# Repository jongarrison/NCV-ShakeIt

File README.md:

# NCV-ShakeIt
## (Non Contact Voltage Detecting Time Delayed Relay With Audio Feedback)

<div style="width: 100%; text-align: center;">
    
</div>

This device is designed to turn on two relays (currently for a single two phase motor) after detecting that another AC device has shut off. The running of the other AC device is detected using a Non-contact Voltage (NCV) detector. When the device is about to trigger the relays, it plays some audio feedback (mp3 files) to let people know the motor is about to run.

Basic functions:
* Device has an antenna for detecting 60hz AC power in a nearby wire. If AC is detected for longer than a minimum threshold the system is ready to trigger when the AC next shuts off. The sensitivity of the AC detection is controlled by a potentiometer knob.
* The device waits for some interval while the main motor system spools down. During this spool down period audio is played to indicate what is happening.
* After the spool down period, two relays are turned on for an interval set by another potentiometer knob. 

# Technical Details

### Non-contact Voltage Detector circuit and algorithm
* Based on this very cool project: https://www.instructables.com/Contactless-AC-Detector/

### PCB Design
* Kicad files are provided in ./PCB_NCV-ShakeIt

<div style="width: 100%; text-align: center;">
    
</div>

### Enclosure Design
* Done in Rhino3D Grasshopper. Files found in ./ShakeIt_enclosure

<div style="width: 100%; text-align: center;">
    
</div>

### Microcontroller
* [Seeed Xiao SAMD21 board](https://wiki.seeedstudio.com/Seeeduino-XIAO/) - [Pinout](https://wiki.seeedstudio.com/Seeeduino-XIAO/#hardware-overview)

### MP3 Playback - DFPlayer
* [Usage Tips](https://reprage.com/posts/2018-05-08-dfplayer-mini-cheat-sheet/)

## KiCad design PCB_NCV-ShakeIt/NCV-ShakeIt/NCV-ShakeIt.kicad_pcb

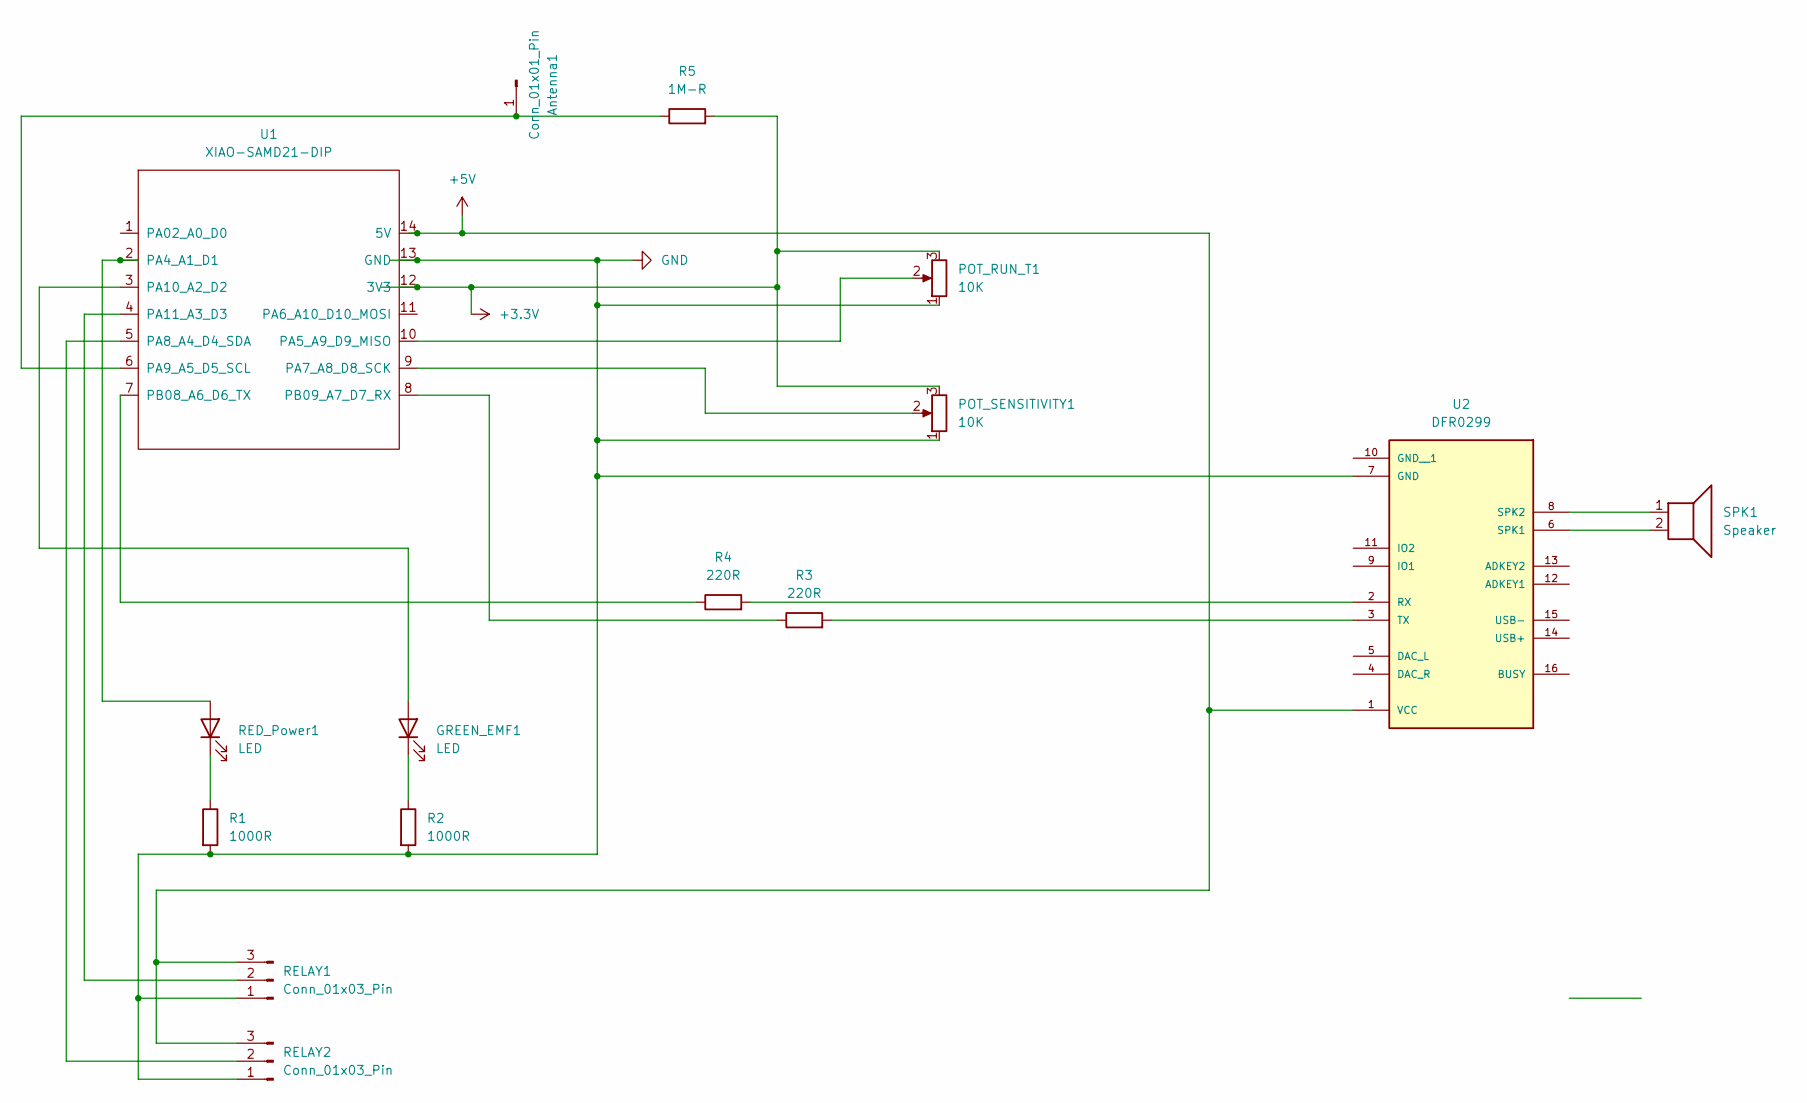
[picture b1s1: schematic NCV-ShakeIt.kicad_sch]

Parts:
Antenna1: Conn_01x01_Pin; PinHeader_1x01_P2.54mm_Vertical
GREEN_EMF1: LED; LED_D5.0mm
POT_RUN_T1: 10K; JG-3Pin-Pot-11mmOuterPins
POT_SENSITIVITY1: 10K; JG-3Pin-Pot-11mmOuterPins
R1, R2: 1000R; R_Axial_DIN0207_L6.3mm_D2.5mm_P10.16mm_Horizontal
R3, R4: 220R; R_Axial_DIN0207_L6.3mm_D2.5mm_P10.16mm_Horizontal
R5: 1M-R; R_Axial_DIN0207_L6.3mm_D2.5mm_P10.16mm_Horizontal
RED_Power1: LED; LED_D5.0mm
RELAY1, RELAY2: Conn_01x03_Pin; PinHeader_1x03_P2.54mm_Vertical
SPK1: Speaker; PinHeader_1x02_P2.54mm_Vertical
U1: XIAO-SAMD21-DIP
U2: DFR0299; MODULE_DFR0299

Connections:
+3.3V: POT_RUN_T1.3, POT_SENSITIVITY1.3, R5.2, U1.12 (3V3)
+5V: RELAY1.3, RELAY2.3, U1.14 (5V), U2.1 (VCC)
GND: POT_RUN_T1.1, POT_SENSITIVITY1.1, R1.2, R2.2, RELAY1.1, RELAY2.1, U1.13 (GND), U2.7 (GND); also elsewhere on the board
unnamed: Antenna1.1, R5.1, U1.6 (PA9_A5_D5_SCL)
unnamed: GREEN_EMF1.2 (A), U1.3 (PA10_A2_D2)
unnamed: GREEN_EMF1.1 (K), R2.1
unnamed 6: U1.1 (PA02_A0_D0); also elsewhere on the board
unnamed: RED_Power1.2 (A), U1.2 (PA4_A1_D1)
unnamed: R1.1, RED_Power1.1 (K)
unnamed: RELAY1.2, U1.4 (PA11_A3_D3)
unnamed: RELAY2.2, U1.5 (PA8_A4_D4_SDA)
unnamed: POT_RUN_T1.2, U1.10 (PA5_A9_D9_MISO)
unnamed: POT_SENSITIVITY1.2, U1.9 (PA7_A8_D8_SCK)
unnamed: R4.1, U1.7 (PB08_A6_D6_TX)
unnamed: R3.1, U1.8 (PB09_A7_D7_RX)
unnamed: R4.2, U2.2 (RX)
unnamed: SPK1.2, U2.6 (SPK1)
unnamed: SPK1.1, U2.8 (SPK2)
unnamed: R3.2, U2.3 (TX)

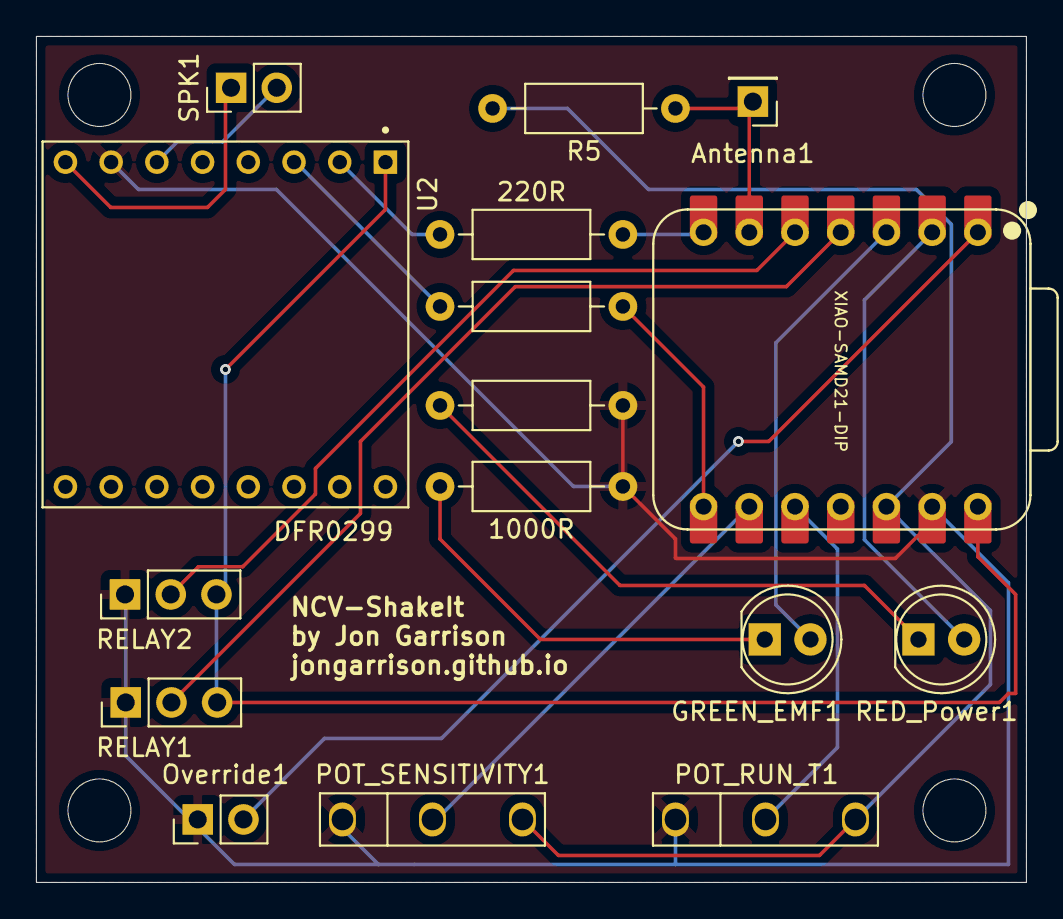
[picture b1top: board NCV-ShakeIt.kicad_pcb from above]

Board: 2 copper layers, 55.0 x 47.0 mm, 16 parts (0 on the bottom side), 19 nets.

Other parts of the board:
Override1: Conn_01x02_Pin; PinHeader_1x02_P2.54mm_Vertical

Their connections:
GND: Override1.1; also elsewhere on the board
unnamed 6: Override1.2; also elsewhere on the board

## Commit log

2025-04-09 Including more kicad files and improving the potentiometer adjustment code
2025-04-17 Checking in mostly grasshopper enclosure generation stuff and some clean up to the main code
2025-04-18 Adding to docs, fixing code, renaming things to be more clear
2025-04-20 Added AceButton to allow various button behaviors. Added a long press volume set feature. Persisted volume setting with FlashStorage library, very cool
2025-04-24 organizing the 3D elements
2025-04-25 Creating a proper state machine to handle transitions during the now longer spind down interval.
2025-04-26 Adding a pic and minor changes
2025-04-26 adding image
2025-04-28 More updates for the state machine and some notes
2025-04-28 More pics
2025-04-28 And more pics
